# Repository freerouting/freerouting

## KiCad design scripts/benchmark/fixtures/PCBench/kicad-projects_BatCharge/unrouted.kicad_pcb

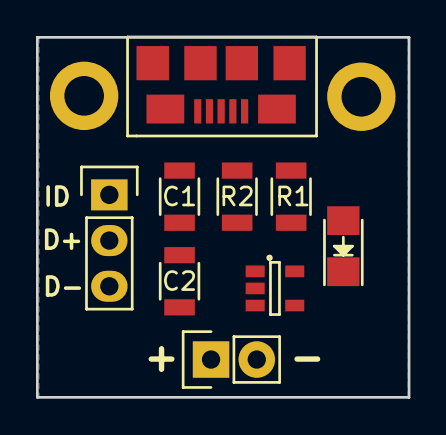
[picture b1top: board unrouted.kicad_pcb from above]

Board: 2 copper layers, 20.7 x 20.0 mm, 11 parts (0 on the bottom side), 9 nets, no tracks yet.

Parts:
C1, C2: R_1206
D1: LED; LED_1206
Noname_1: micro-usb-fci
Noname_2, Noname_3: MountingHole_2.2mm_M2_ISO14580_Pad
Noname_4: Pin_Header_Straight_1x02
Noname_5: Pin_Header_Straight_1x03
R1, R2: R_1206
U1: SOT-23-5

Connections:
GND: C1.2, C2.2, Noname_1.5, Noname_1.6, Noname_4.2, R2.2, U1.2
unnamed: C1.1, C2.1, Noname_4.1, U1.3
unnamed: D1.1, U1.1
unnamed: D1.2, R1.2
unnamed: Noname_1.4, Noname_5.1
unnamed: Noname_1.3, Noname_5.2
unnamed: Noname_1.2, Noname_5.3
unnamed: Noname_1.1, R1.1, U1.4
unnamed: R2.1, U1.5

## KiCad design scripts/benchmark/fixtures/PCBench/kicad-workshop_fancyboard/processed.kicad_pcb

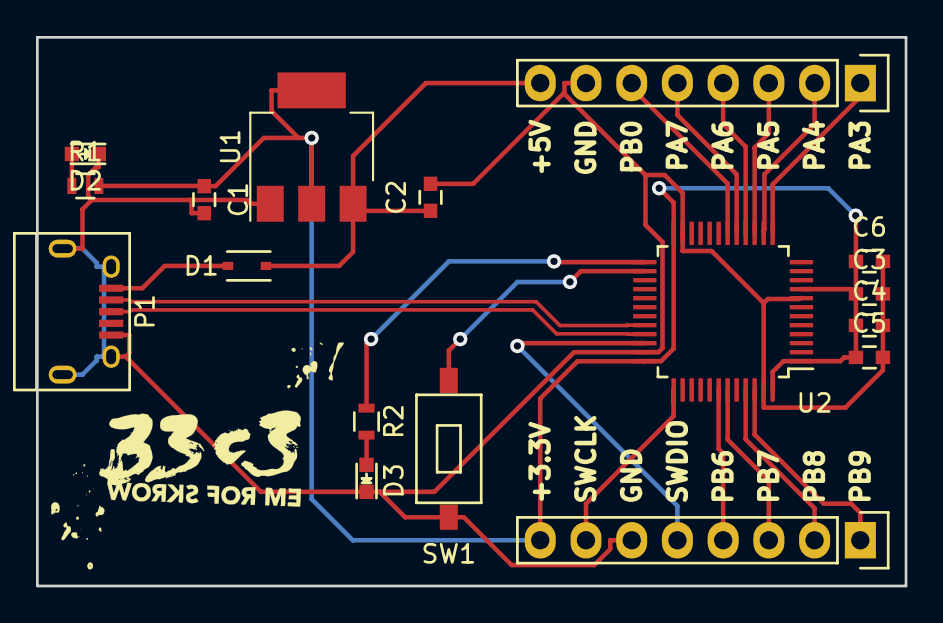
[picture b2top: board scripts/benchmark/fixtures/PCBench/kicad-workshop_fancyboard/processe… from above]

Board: 2 copper layers, 48.3 x 30.5 mm, 17 parts (0 on the bottom side), 22 nets.

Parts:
C1, C2, C3, C4, C6: 100n; C_0603
C5: 4.7u; C_0603
D1: D; SOD-323
D2, D3: LED; LED_0603
P1: USB_OTG; USB_Micro-B
P2, P3: CONN_01X08; Pin_Header_Straight_1x08
R1, R2: 360; R_0603
SW1: SW_Push; SmallButton
U1: AP111733; SOT-223
U2: STM32F072C8Tx; LQFP-48_7x7mm_Pitch0.5mm

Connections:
+3V3: C1.1, C3.1, C4.1, C5.1, C6.1, P3.8, R1.2, U1.2, U1.4, U2.1, U2.9, U2.24, U2.36, U2.48
+5V: C2.1, D1.1, P2.8, U1.3
/BTN1: SW1.1, U2.26
/LED1: R2.2, U2.25
/PA3: P2.1, U2.13
/PA4: P2.2, U2.14
/PA5: P2.3, U2.15
/PA6: P2.4, U2.16
/PA7: P2.5, U2.17
/PB0: P2.6, U2.18
/PB6: P3.4, U2.42
/PB7: P3.3, U2.43
/PB8: P3.2, U2.45
/PB9: P3.1, U2.46
/SWCLK: P3.7, U2.37
/SWDIO: P3.5, U2.34
/USB_D+: P1.3, U2.33
/USB_D-: P1.2, U2.32
GND: C1.2, C2.2, C3.2, C4.2, C5.2, C6.2, D2.1, D3.1, P1.5, P1.6, P2.7, P3.6, SW1.2, U1.1, U2.8, U2.23, U2.35, U2.47
unnamed: D1.2, P1.1
unnamed: D2.2, R1.1
unnamed: D3.2, R2.1

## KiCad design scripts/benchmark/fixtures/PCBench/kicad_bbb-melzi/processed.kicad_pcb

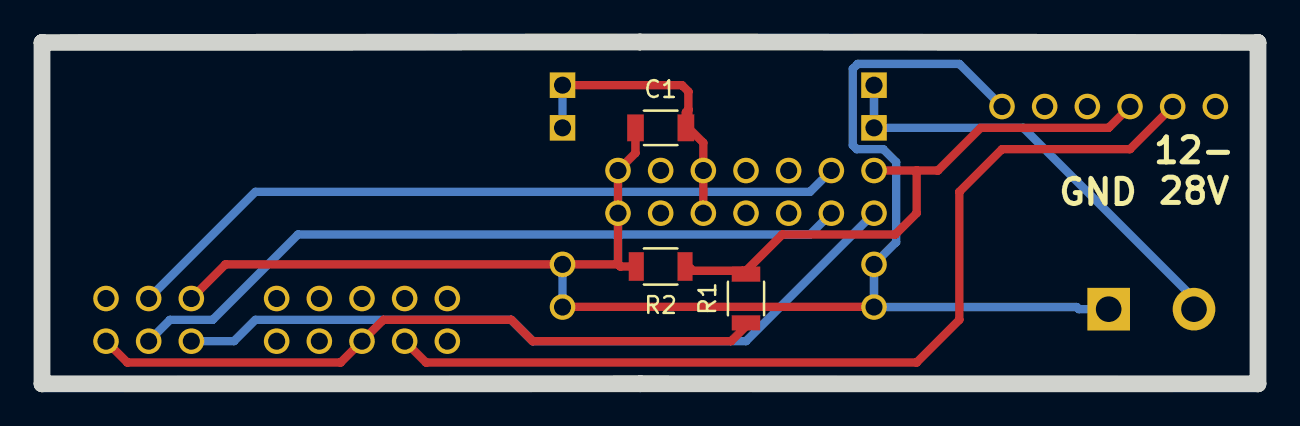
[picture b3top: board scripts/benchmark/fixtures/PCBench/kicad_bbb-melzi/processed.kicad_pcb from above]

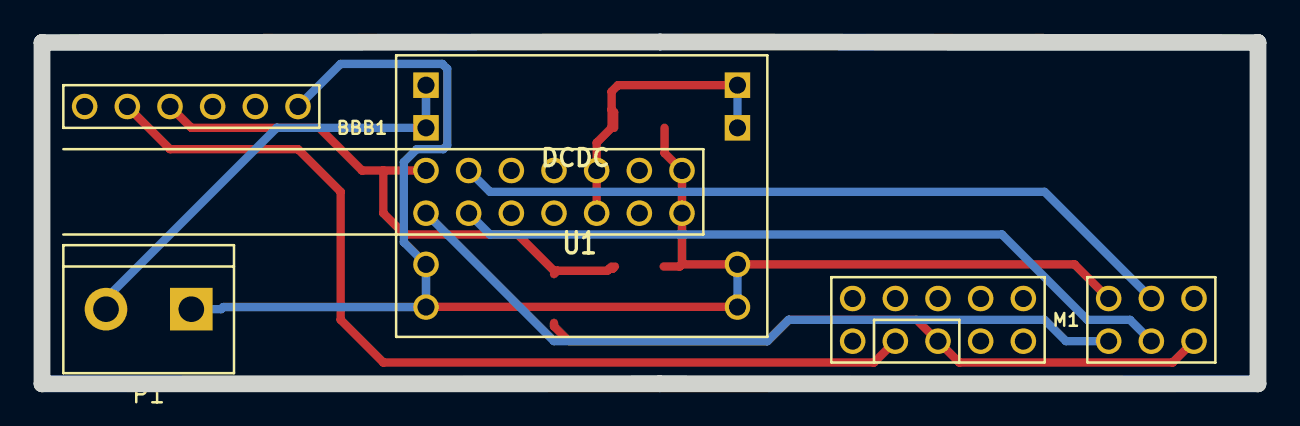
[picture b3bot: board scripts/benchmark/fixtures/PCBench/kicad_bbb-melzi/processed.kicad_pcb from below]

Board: 2 copper layers, 72.4 x 20.4 mm, 7 parts (4 on the bottom side), 9 nets.

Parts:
BBB1: BBB
C1: C; C_1206
M1: MELZI; Melzi
P1: CONN_2; bornier2
R1, R2: R; R_1206
U1: DCDC

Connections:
/GND: BBB1.GND, C1.1, M1.GND, P1.1, R2.2, U1.GND, U1.GND2
/MISO: M1.MISO, M1.TxD, R1.1
/MISO3: BBB1.50, BBB1.RxD, R1.2, R2.1
/MOSI: BBB1.60, M1.MOSI
/Reset: BBB1.31, M1.~RST
/SCK: BBB1.30, M1.SCK
/VDD: BBB1.VDD, C1.2, U1.Vout
/VIN: P1.2, U1.Vin
unnamed: BBB1.TxD, M1.RxD
